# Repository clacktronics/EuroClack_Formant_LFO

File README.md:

# EuroClack Formant LFO clone

A copy of the Elektor Formant LFO modified for Eurorack

**STILL WIP** This text will be gone when it is tested and working

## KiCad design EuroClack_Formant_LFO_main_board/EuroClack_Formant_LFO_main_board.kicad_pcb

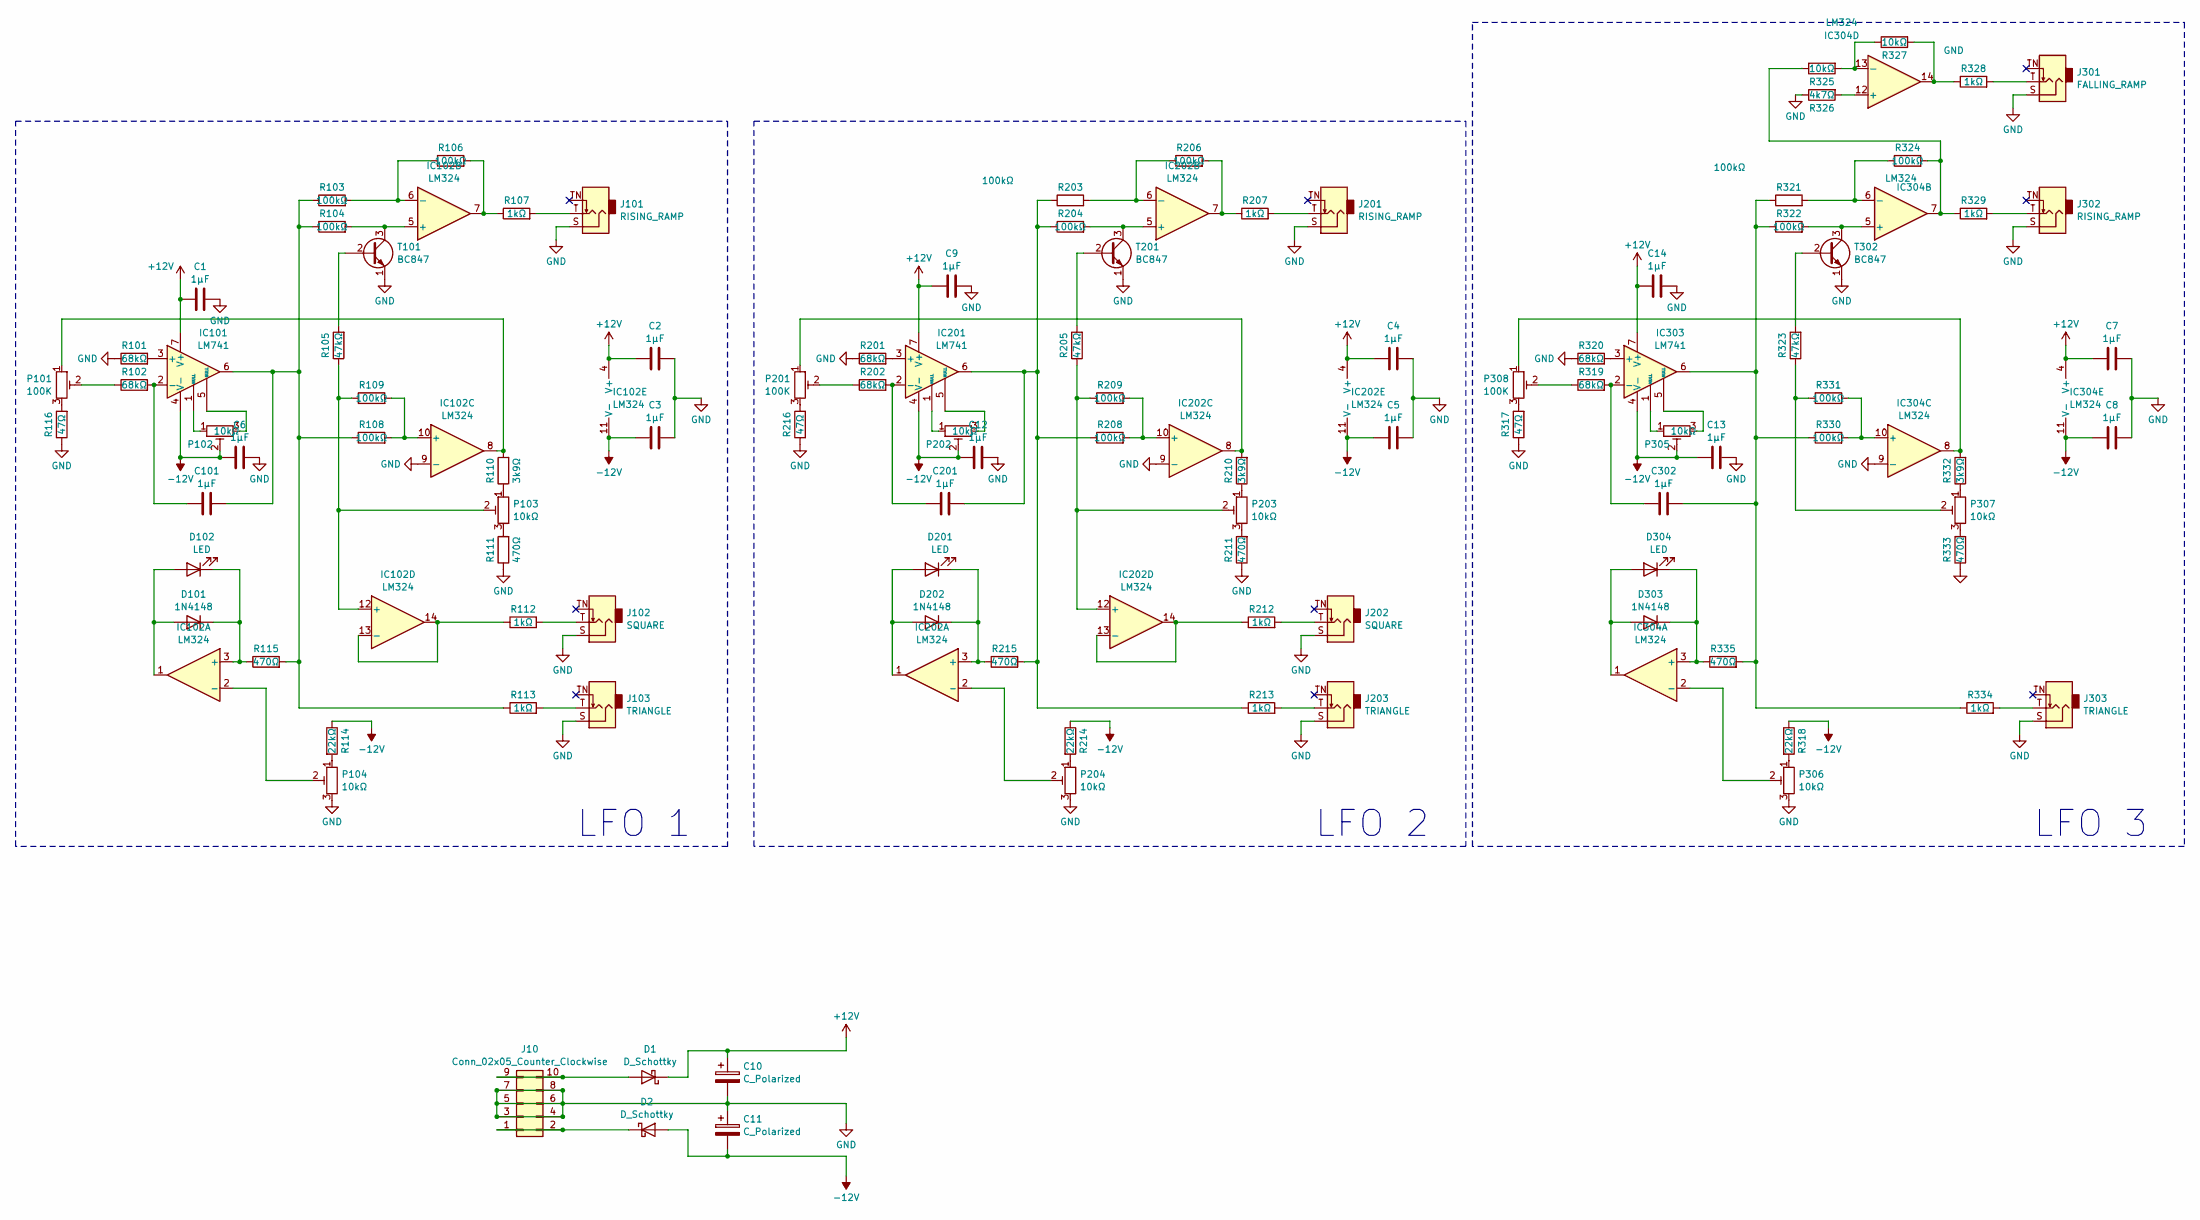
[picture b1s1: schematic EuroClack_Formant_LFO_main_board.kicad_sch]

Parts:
C1, C2, C3, C4, C5, C6, C7, C8, C9, C12, C13, C14, C101, C201, C302: 1μF; C_0805_2012Metric
C10, C11: C_Polarized; CP_Elec_4x3
D1, D2: D_Schottky; D_SMA
D101, D202, D303: 1N4148; D_SOD-123
D102, D201, D304: LED; LED_D5.0mm
IC101, IC201, IC303: LM741; SOIC-8_3.9x4.9mm_P1.27mm
IC102, IC202, IC304: LM324; SOIC-14_3.9x8.7mm_P1.27mm
J10: Conn_02x05_Counter_Clockwise; IDC-Header_2x05_P2.54mm_Vertical
J101, J201, J302: RISING_RAMP; Jack_3.5mm_QingPu_WQP-PJ366ST_Vertical
J102, J202: SQUARE; Jack_3.5mm_QingPu_WQP-PJ366ST_Vertical
J103, J203, J303: TRIANGLE; Jack_3.5mm_QingPu_WQP-PJ366ST_Vertical
J301: FALLING_RAMP; Jack_3.5mm_QingPu_WQP-PJ366ST_Vertical
P101, P201, P308: 100K; POT_TH_Alps_RK09K_Single_Vertical
P102, P103, P104, P202, P203, P204, P305, P306, P307: 10kΩ; Potentiometer_Bourns_3296W_Vertical
R101, R102, R201, R202, R319, R320: 68kΩ; R_0603_1608Metric
R103, R104, R106, R108, R109, R203, R204, R206, R208, R209, R321, R322, R324, R330, R331: 100kΩ; R_0603_1608Metric
R105, R205, R323: 47kΩ; R_0603_1608Metric
R107, R112, R113, R207, R212, R213, R328, R329, R334: 1kΩ; R_0603_1608Metric
R110, R210, R332: 3k9Ω; R_0603_1608Metric
R111, R115, R211, R215, R333, R335: 470Ω; R_0603_1608Metric
R114, R214, R318: 22kΩ; R_0603_1608Metric
R116, R216, R317: 47Ω; R_0603_1608Metric
R325, R327: 10kΩ; R_0603_1608Metric
R326: 4k7Ω; R_0603_1608Metric
T101, T201, T302: BC847; SOT-23

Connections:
+12V: C1.1, C2.1, C4.1, C7.1, C9.1, C10.1, C14.1, D1.1 (K), IC101.7 (V+), IC102.4 (V+), IC201.7 (V+), IC202.4 (V+), IC303.7 (V+), IC304.4 (V+)
-12V: C3.1, C5.1, C6.1, C8.1, C11.2, C12.1, C13.1, D2.2 (A), IC101.4 (V-), IC102.11 (V-), IC201.4 (V-), IC202.11 (V-), IC303.4 (V-), IC304.11 (V-), P102.2, P202.2, P305.2, R114.1, R214.1, R318.1
GND: C1.2, C2.2, C3.2, C4.2, C5.2, C6.2, C7.2, C8.2, C9.2, C10.2, C11.1, C12.2, C13.2, C14.2, IC102.9 (-), IC202.9 (-), IC304.9 (-), J10.3, J10.4, J10.5, J10.6, J10.7, J10.8, J101.S, J102.S, J103.S, J201.S, J202.S, J203.S, J301.S, J302.S, J303.S, P104.3, P204.3, P306.3, R101.1, R111.1, R116.1, R201.1, R211.1, R216.1, R317.1, R320.1, R326.1, R333.1, T101.1 (E), T201.1 (E), T302.1 (E)
unnamed: C101.2, IC101.6, R103.1, R104.1, R108.1, R113.1, R115.2
unnamed: C201.2, IC201.6, R203.1, R204.1, R208.1, R213.1, R215.2
unnamed: C302.2, IC303.6, R321.1, R322.1, R330.1, R334.1, R335.2
unnamed: D1.2 (A), J10.9, J10.10
unnamed: D2.1 (K), J10.1, J10.2
unnamed: D101.2 (A), D102.2 (A), IC102.1
unnamed: D101.1 (K), D102.1 (K), IC102.3 (+), R115.1
unnamed: D201.2 (A), D202.2 (A), IC202.1
unnamed: D201.1 (K), D202.1 (K), IC202.3 (+), R215.1
unnamed: D303.2 (A), D304.2 (A), IC304.1
unnamed: D303.1 (K), D304.1 (K), IC304.3 (+), R335.1
unnamed: IC101.3 (+), R101.2
unnamed: C101.1, IC101.2 (-), R102.2
unnamed: IC101.1 (NULL), P102.1
unnamed: IC101.5 (NULL), P102.3
unnamed: IC102.7, R106.2, R107.1
unnamed: IC102.8, P101.1, R110.2
unnamed: IC102.2 (-), P104.2
unnamed: IC102.5 (+), R104.2, T101.3 (C)
unnamed: IC102.6 (-), R103.2, R106.1
unnamed: IC102.10 (+), R108.2, R109.2
unnamed: IC102.12 (+), P103.2, R105.1, R109.1
unnamed: IC102.13 (-), IC102.14, R112.1
unnamed: IC201.3 (+), R201.2
unnamed: C201.1, IC201.2 (-), R202.2
unnamed: IC201.1 (NULL), P202.1
unnamed: IC201.5 (NULL), P202.3
unnamed: IC202.7, R206.2, R207.1
unnamed: IC202.8, P201.1, R210.2
unnamed: IC202.2 (-), P204.2
unnamed: IC202.5 (+), R204.2, T201.3 (C)
unnamed: IC202.6 (-), R203.2, R206.1
unnamed: IC202.10 (+), R208.2, R209.2
unnamed: IC202.12 (+), P203.2, R205.1, R209.1
unnamed: IC202.13 (-), IC202.14, R212.1
unnamed: IC303.3 (+), R320.2
unnamed: C302.1, IC303.2 (-), R319.2
unnamed: IC303.1 (NULL), P305.1
unnamed: IC303.5 (NULL), P305.3
unnamed: IC304.7, R324.2, R325.1, R329.1
unnamed: IC304.8, P308.1, R332.2
unnamed: IC304.14, R327.2, R328.1
unnamed: IC304.2 (-), P306.2
unnamed: IC304.5 (+), R322.2, T302.3 (C)
unnamed: IC304.6 (-), R321.2, R324.1
unnamed: IC304.10 (+), R330.2, R331.2
unnamed: IC304.12 (+), R326.2
unnamed: IC304.13 (-), R325.2, R327.1
unnamed: J101.T, R107.2
unnamed: J102.T, R112.2
unnamed: J103.T, R113.2
unnamed: J201.T, R207.2
unnamed: J202.T, R212.2
unnamed: J203.T, R213.2
unnamed: J301.T, R328.2
unnamed: J302.T, R329.2
unnamed: J303.T, R334.2
unnamed: P101.2, R102.1
unnamed: P101.3, R116.2
unnamed: P103.1, R110.1
unnamed: P103.3, R111.2
unnamed: P104.1, R114.2
unnamed: P201.2, R202.1
unnamed: P201.3, R216.2
unnamed: P203.1, R210.1
unnamed: P203.3, R211.2
unnamed: P204.1, R214.2
unnamed: P306.1, R318.2
unnamed: P307.1, R332.1
unnamed: P307.2, R323.1, R331.1
unnamed: P307.3, R333.2
unnamed: P308.2, R319.1
unnamed: P308.3, R317.2
unnamed: R105.2, T101.2 (B)
unnamed: R205.2, T201.2 (B)
unnamed: R323.2, T302.2 (B)

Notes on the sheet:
LFO 2
LFO 1
LFO 3

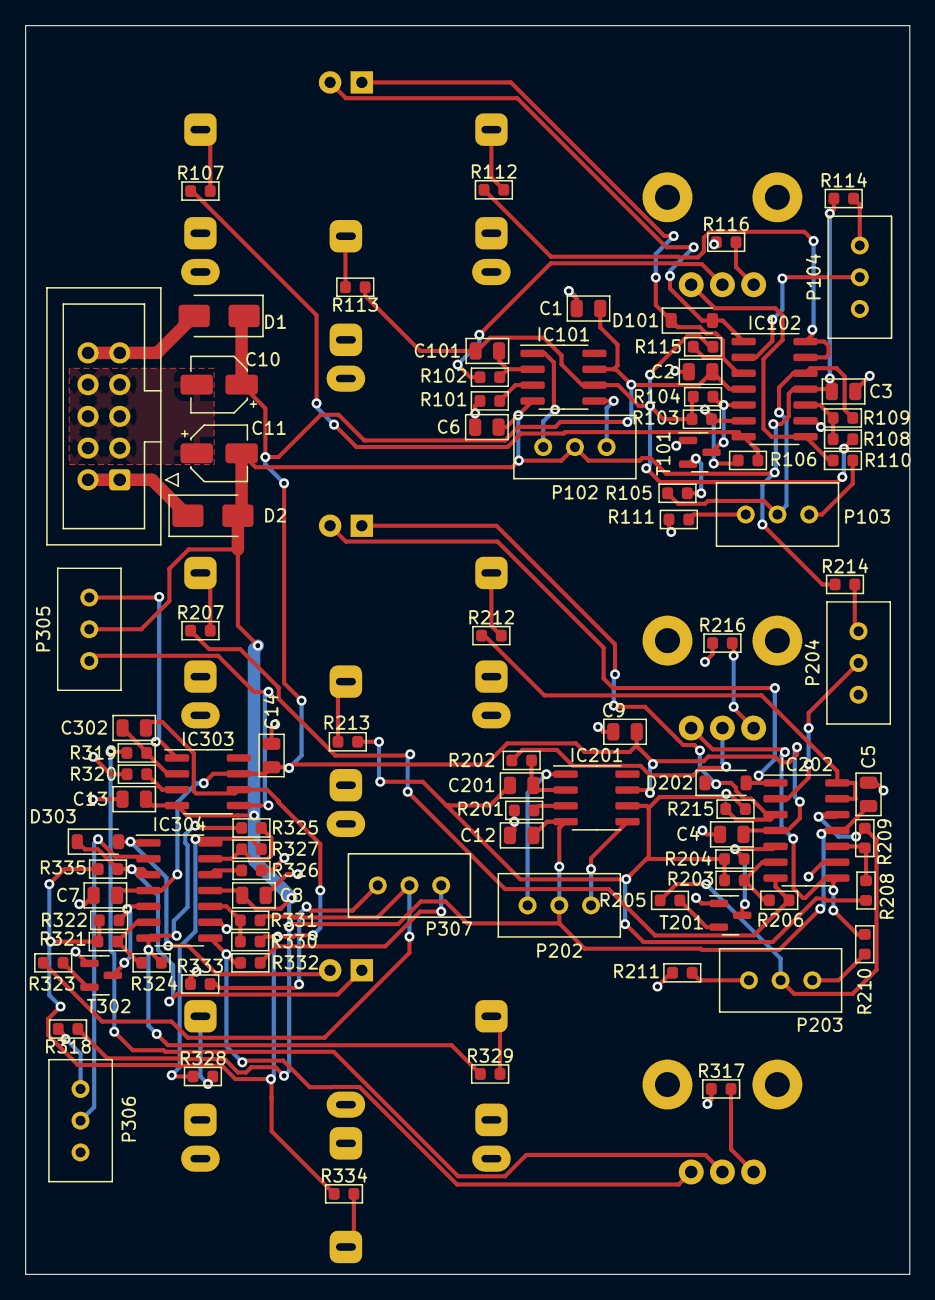
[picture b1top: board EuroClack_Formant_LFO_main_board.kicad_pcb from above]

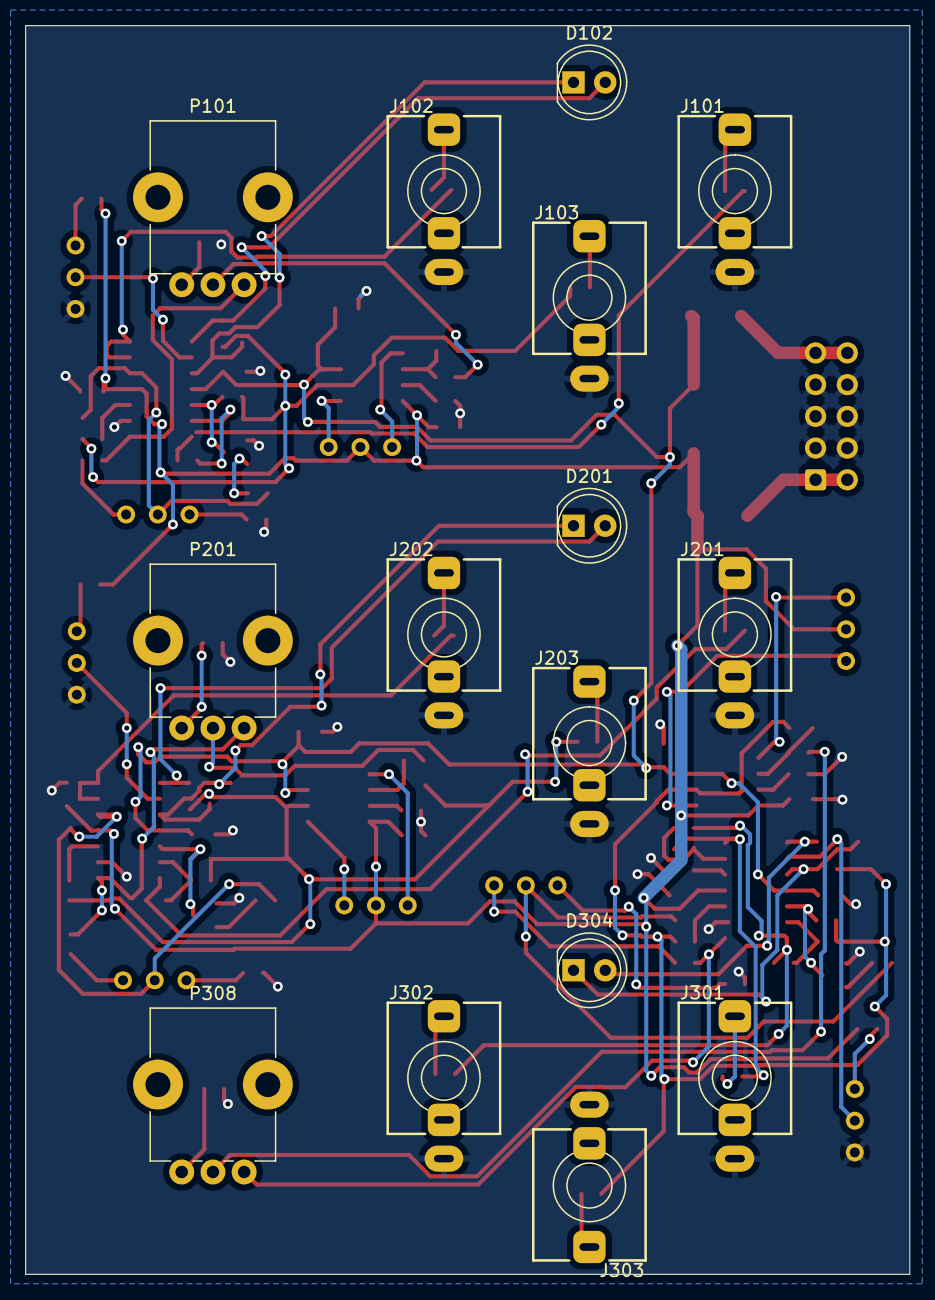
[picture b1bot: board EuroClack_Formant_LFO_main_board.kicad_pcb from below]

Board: 2 copper layers, 70.8 x 100.0 mm, 107 parts (15 on the bottom side), 79 nets.

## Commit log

2024-03-28 Initital files, untested design
2024-03-28 Added schematic pdf and made tweaks
